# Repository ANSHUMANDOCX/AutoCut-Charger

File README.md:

# AutoCut-Charger
## Plan
This board is designed for trickle charging a lead acid battery and turn of the charging automatically once it reaches the max rated voltage of the battery automatically. the cutoff voltage can be set using the trim pot.
## How to use 
Its pretty simple to use we just need to connect a 12-0-12 transformer to the circuit and the ac voltage will be rectified from Full bridge rectifier then using RV1 we set the output voltage and measure it using a multimeter one we are at it then we will use the rv2 to set the cutoff voltage we will know that we are at the cutoff when we will see the full led turned on and the relay clicks.
## Connection Guide 
The connections are pretty straight froward the 12-0-12 from the center tap transformer goes to the 3 pin terminal of the PCB and the battery +ve and -ve is connected to the 2 pin terminal on the labelled pins

## Parts Requried 
- 12-0-12 transformer 
- 12v relay
- LM317t voltage regulator
- MJE2955 transistor  

## PCB and Schematic and CAD

# BOM 

| Name                                                                                           | Qty | Vendor     | Price ($) |
| ---------------------------------------------------------------------------------------------- | --- | ---------- | --------- |
| ALL BOM parts mosfet,resistor capacitors etc  |  | LCSC | 14     |
| [12-0-12 3A](https://robu.in/product/high-quality-12v-0v-12v-3a-center-tapped-stepdown-transformer/) | 1   | ROBU      | 6      |
|PCB||JLCPCB|5|
|Total|||25|

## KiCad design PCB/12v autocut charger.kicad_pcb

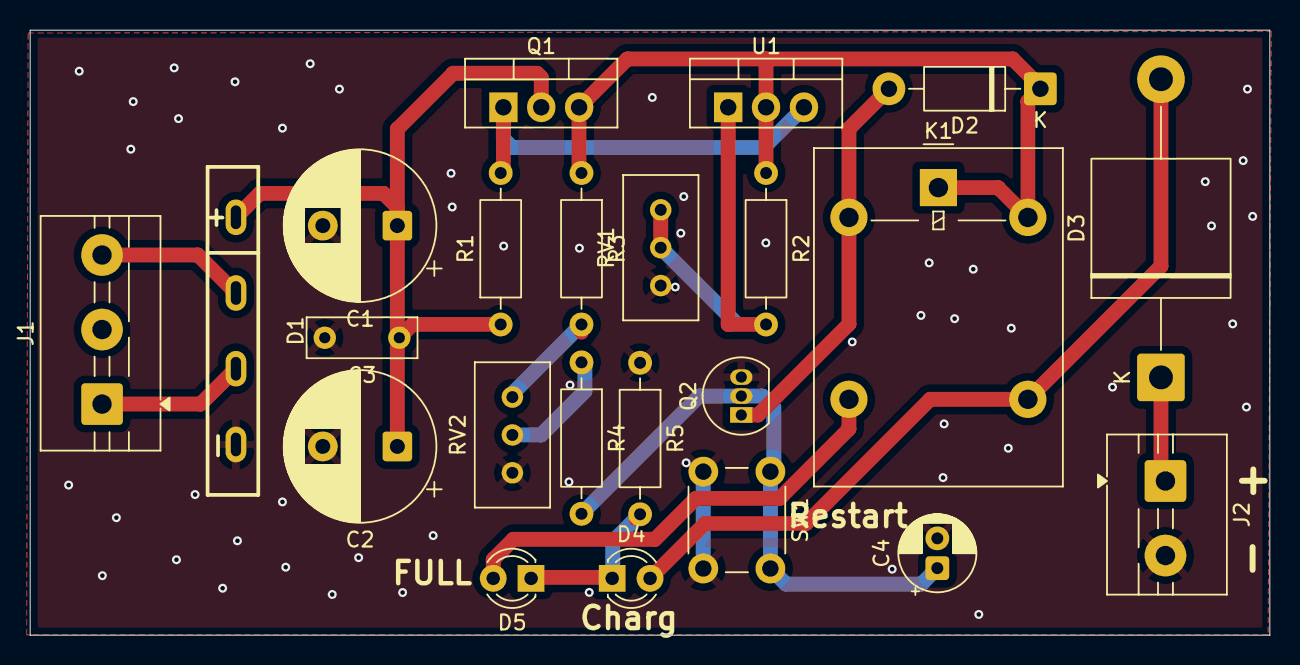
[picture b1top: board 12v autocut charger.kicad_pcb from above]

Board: 2 copper layers, 83.1 x 40.6 mm, 23 parts (0 on the bottom side), 15 nets.

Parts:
C1, C2: 1000uF; CP_Radial_D10.0mm_P5.00mm
C3: 100nf; C_Rect_L7.2mm_W2.5mm_P5.00mm
C4: 10uF; CP_Radial_D5.0mm_P2.00mm
D1: GBU1508A-B1-0000; GBU_4P-L22.0-W3.6-P5.08
D2: D; D_DO-41_SOD81_P10.16mm_Horizontal
D3: 10A; D_P600_R-6_P20.00mm_Horizontal
D4: CHRG; LED_D3.0mm
D5: FULL; LED_D3.0mm
J1: Conn_01x03_Socket; TerminalBlock_MaiXu_MX126-5.0-03P_1x03_P5.00mm
J2: Conn_01x02_Socket; TerminalBlock_MaiXu_MX126-5.0-02P_1x02_P5.00mm
K1: G5LE-1; Relay_SPDT_Omron-G5LE-1
Q1: MJE2955; TO-220-3_Vertical
Q2: BC547; TO-92_Inline
R1: 10R; R_Axial_DIN0207_L6.3mm_D2.5mm_P10.16mm_Horizontal
R2: 220R; R_Axial_DIN0207_L6.3mm_D2.5mm_P10.16mm_Horizontal
R3: 10K; R_Axial_DIN0207_L6.3mm_D2.5mm_P10.16mm_Horizontal
R4: 1K; R_Axial_DIN0207_L6.3mm_D2.5mm_P10.16mm_Horizontal
R5: R; R_Axial_DIN0207_L6.3mm_D2.5mm_P10.16mm_Horizontal
RV1, RV2: 10K; Potentiometer_Bourns_3296W_Vertical
SW1: RESTART; SW_PUSH_6mm
U1: LM317_TO-220; TO-220-3_Vertical

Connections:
GND: C1.2, C2.2, C3.2, C4.2, D1.4 (-), J2.2, Q2.3 (E), R5.1, RV1.3, RV2.3, SW1.2
unnamed: C1.1, C2.1, C3.1, D1.1 (+), Q1.2 (C), R1.1
unnamed: D2.2 (A), K1.2, Q2.1 (C)
unnamed: D2.1 (K), K1.1, K1.5, Q1.3 (E), R2.1, R3.1, U1.2 (VO)
unnamed: D3.2 (A), D4.2 (A), K1.4
unnamed: D3.1 (K), J2.1
unnamed: D4.1 (K), D5.1 (K), R5.2
unnamed: D5.2 (A), K1.3
unnamed: D1.3 (AC), J1.1
unnamed: D1.2 (AC), J1.3
unnamed: Q1.1 (B), R1.2, U1.3 (VI)
unnamed: C4.1, Q2.2 (B), R4.2, SW1.1
unnamed: R3.2, RV2.1
unnamed: R4.1, RV2.2
unnamed: R2.2, RV1.1, RV1.2, U1.1 (ADJ)

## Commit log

2026-01-25 Add BOM.csv with component details and pricing
2026-01-25 Add journal entries for circuit schematic and PCB work
    Documented the progress of circuit design and PCB routing, including time spent and challenges faced.
2026-01-25 Update BOM parts quantity and total price
2026-03-04 Add connection guide to README
    Added a connection guide section to the README.
